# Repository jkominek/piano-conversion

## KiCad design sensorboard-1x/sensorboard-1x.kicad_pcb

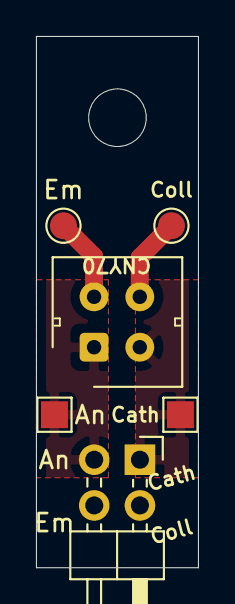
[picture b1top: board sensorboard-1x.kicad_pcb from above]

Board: 2 copper layers, 9.0 x 29.5 mm, 7 parts (0 on the bottom side), 4 nets.

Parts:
An1: TestPoint; TestPoint_Pad_1.5x1.5mm
Cath1: TestPoint; TestPoint_Pad_1.5x1.5mm
Coll1: TestPoint; TestPoint_Pad_D1.5mm
Emit1: TestPoint; TestPoint_Pad_D1.5mm
H1: MountingHole; MountingHole_3.2mm_M3
J1: Conn_02x02_Odd_Even; Pin_Header_Angled_2x02_Pitch2.54mm
U1: CNY70; Vishay_CNY70

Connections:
/Anode: An1.1, J1.3, U1.1
/Cathode: Cath1.1, J1.1, U1.2
/Collector: Coll1.1, J1.2, U1.3
/Emitter: Emit1.1, J1.4, U1.4

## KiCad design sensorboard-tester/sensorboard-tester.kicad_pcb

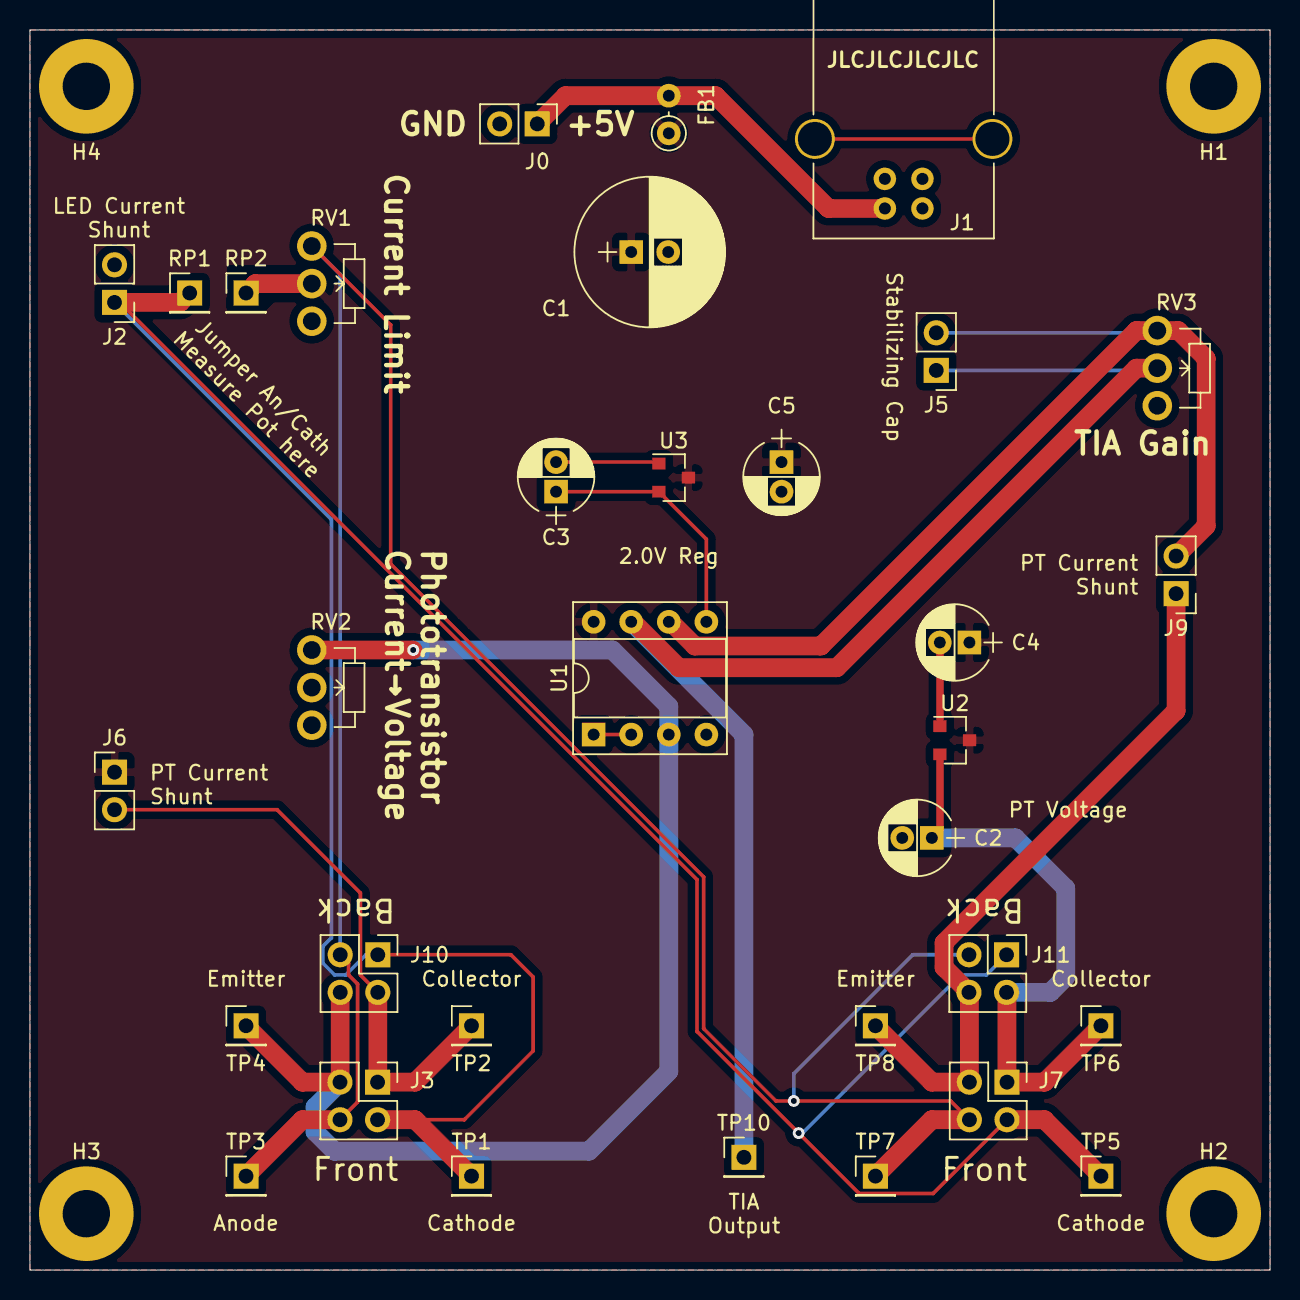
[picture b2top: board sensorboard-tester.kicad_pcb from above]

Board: 2 copper layers, 83.8 x 83.8 mm, 37 parts (0 on the bottom side), 13 nets.

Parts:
C1: C_Small; CP_Radial_D10.0mm_P2.50mm
C2, C4: 10uF; CP_Radial_D5.0mm_P2.00mm
C3, C5: 1uF; CP_Radial_D5.0mm_P2.00mm
FB1: Ferrite_Bead_Small; L_Axial_L5.3mm_D2.2mm_P2.54mm_Vertical_Vishay_IM-1
H1, H2, H3, H4: MountingHole_Pad; MountingHole_3.2mm_M3_Pad
J0: Power; Pin_Header_Straight_1x02_Pitch2.54mm
J1: USB_B
J2: LEDCurrentShunt; Pin_Header_Straight_1x02_Pitch2.54mm
J3, J7, J11: Sensor; Pin_Header_Straight_2x02_Pitch2.54mm
J5: StabilizingCap; Pin_Header_Straight_1x02_Pitch2.54mm
J6, J9: PTCurrentShunt; Pin_Header_Straight_1x02_Pitch2.54mm
J10: MirrorSensor; Pin_Header_Straight_2x02_Pitch2.54mm
RP1, RP2: TestPoint_Probe; Pin_Header_Straight_1x01_Pitch2.54mm
RV1, RV2, RV3: R_POT; Potentiometer_WirePads_Small
TP1, TP2, TP3, TP4, TP5, TP6, TP7, TP8, TP10: TestPoint_Probe; Pin_Header_Straight_1x01_Pitch2.54mm
U1: Opamp_Dual_Generic; DIP-8_W7.62mm_Socket
U2: AP2120N-3.3TRG1; SOT-23
U3: MCP1700T-2002E/TT; SOT-23

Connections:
+3V3: C2.1, J7.1, J11.2, TP6.1, U2.2
+5V: C1.1, C4.1, C5.1, FB1.1, J6.1, RP2.1, RV1.2, U1.8, U2.3, U3.3
/Anode: J3.4, J7.4, J10.3, J11.3, RV1.1, TP3.1, TP7.1
/Cathode: J2.1, J3.2, J7.2, J10.1, J11.1, RP1.1, TP1.1, TP5.1
/Simple/Collector: J3.1, J6.2, J10.2, TP2.1
/Simple/OP+: J3.3, J10.4, RV2.1, TP4.1, U1.3
/Simple/OP-: U1.1, U1.2
/Transimpedance/Emitter: J7.3, J9.1, J11.4, TP8.1
/Transimpedance/OP+: C3.1, U1.5, U3.2
/Transimpedance/OP-: J5.2, J9.2, RV3.1, U1.6
/Transimpedance/OP_OUT: J5.1, RV3.2, TP10.1, U1.7
GND: C1.2, C2.2, C3.2, C4.2, C5.2, H1.1, H2.1, H3.1, H4.1, J0.2, J1.4, J2.2, RV2.2, U1.4, U2.1, U3.1
unnamed: FB1.2, J0.1, J1.1

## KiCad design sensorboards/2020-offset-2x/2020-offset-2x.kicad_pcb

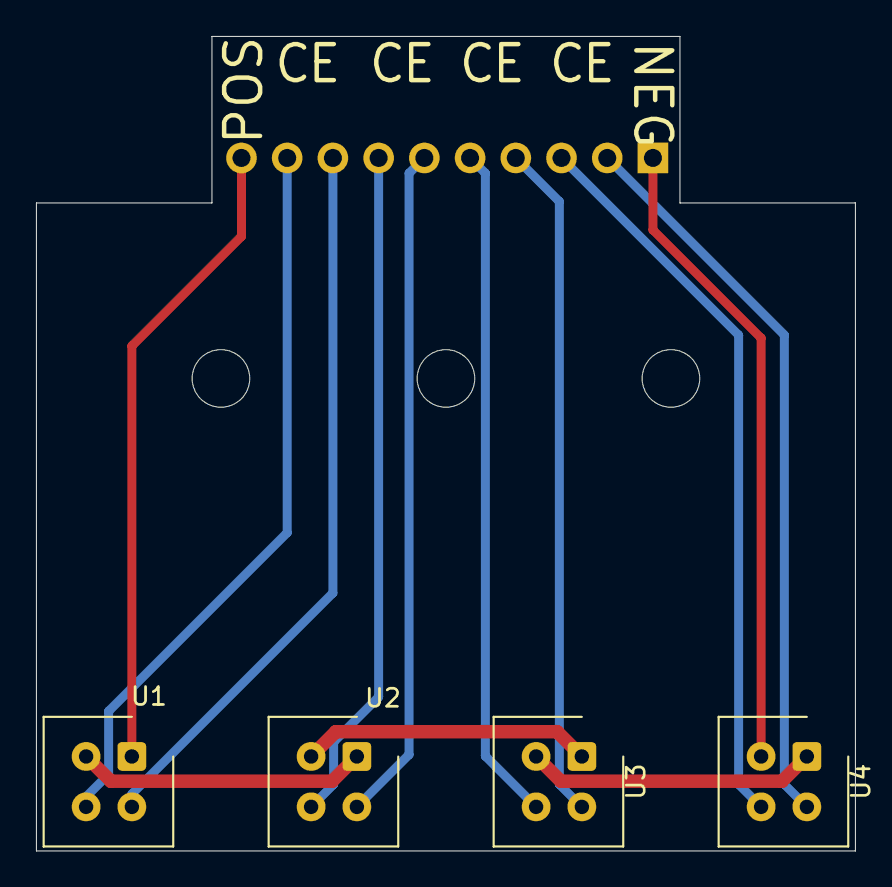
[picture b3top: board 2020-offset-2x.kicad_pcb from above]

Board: 2 copper layers, 45.5 x 45.2 mm, 8 parts (1 on the bottom side), 13 nets.

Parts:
H1, H2, H3: MountingHole; MountingHole_3.2mm_M3
J1: Conn_01x10_Male; Pin_Header_Angled_1x10_Pitch2.54mm
U1, U2, U3, U4: CNY70; Vishay_CNY70

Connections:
/C1: J1.9, U1.3
/C2: J1.7, U2.3
/C3: J1.5, U3.3
/C4: J1.3, U4.3
/E1: J1.8, U1.4
/E2: J1.6, U2.4
/E3: J1.4, U3.4
/E4: J1.2, U4.4
/NEG: J1.1, U4.2
/POS: J1.10, U1.1
unnamed: U1.2, U2.1
unnamed: U2.2, U3.1
unnamed: U3.2, U4.1

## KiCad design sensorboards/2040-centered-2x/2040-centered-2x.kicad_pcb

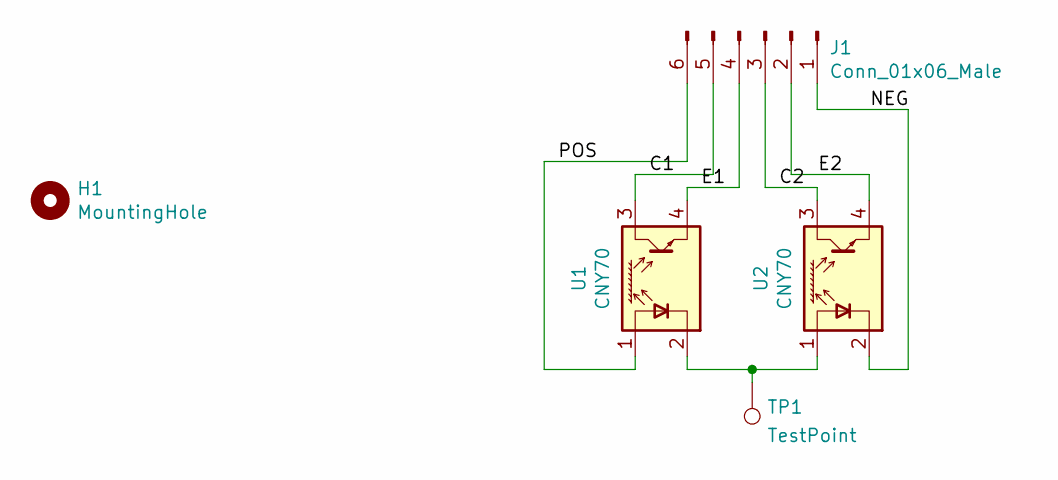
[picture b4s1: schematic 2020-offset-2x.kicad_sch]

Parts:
H1: MountingHole; MountingHole_3.2mm_M3
J1: Conn_01x06_Male; Pin_Header_Angled_1x06_Pitch2.54mm
TP1: TestPoint; TestPoint_Pad_1.0x1.0mm
U1, U2: CNY70; Vishay_CNY70

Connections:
/NEG: J1.1, U2.2 (K)
/POS: J1.6, U1.1 (A)
unnamed: J1.2, U2.4 (E)
unnamed: J1.3, U2.3 (C)
unnamed: J1.4, U1.4 (E)
unnamed: J1.5, U1.3 (C)
unnamed: TP1.1, U1.2 (K), U2.1 (A)

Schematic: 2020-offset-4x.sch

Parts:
H1: MountingHole; MountingHole_3.2mm_M3
J1: Conn_01x06_Male; Pin_Header_Angled_1x06_Pitch2.54mm
U1, U2: CNY70; Vishay_CNY70

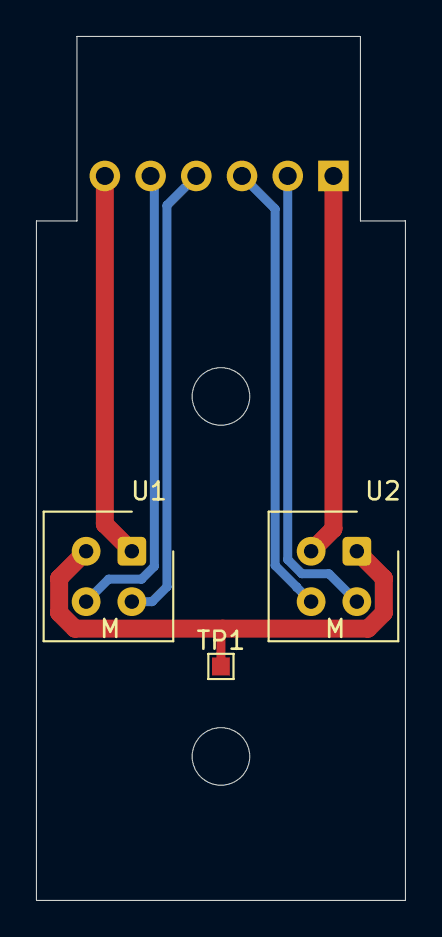
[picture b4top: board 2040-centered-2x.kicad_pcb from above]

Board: 2 copper layers, 20.5 x 48.0 mm, 6 parts (1 on the bottom side), 7 nets.

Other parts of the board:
H2: MountingHole; MountingHole_3.2mm_M3

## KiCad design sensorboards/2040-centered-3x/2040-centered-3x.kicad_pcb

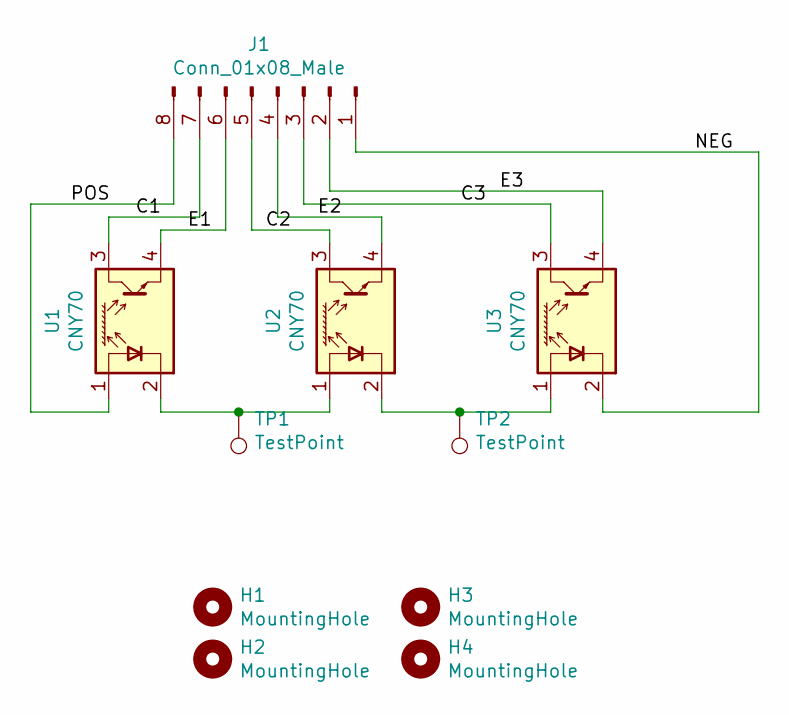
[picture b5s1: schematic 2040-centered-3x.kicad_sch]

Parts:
H1, H2, H3, H4: MountingHole; MountingHole_3.2mm_M3
J1: Conn_01x08_Male; PinHeader_1x08_P2.54mm_Horizontal
TP1, TP2: TestPoint; TestPoint_Pad_1.0x1.0mm
U1, U2, U3: CNY70; Vishay_CNY70

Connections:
/C1: J1.7, U1.3 (C)
/C2: J1.5, U2.3 (C)
/C3: J1.3, U3.3 (C)
/E1: J1.6, U1.4 (E)
/E2: J1.4, U2.4 (E)
/E3: J1.2, U3.4 (E)
/NEG: J1.1, U3.2 (K)
/POS: J1.8, U1.1 (A)
unnamed: TP1.1, U1.2 (K), U2.1 (A)
unnamed: TP2.1, U2.2 (K), U3.1 (A)

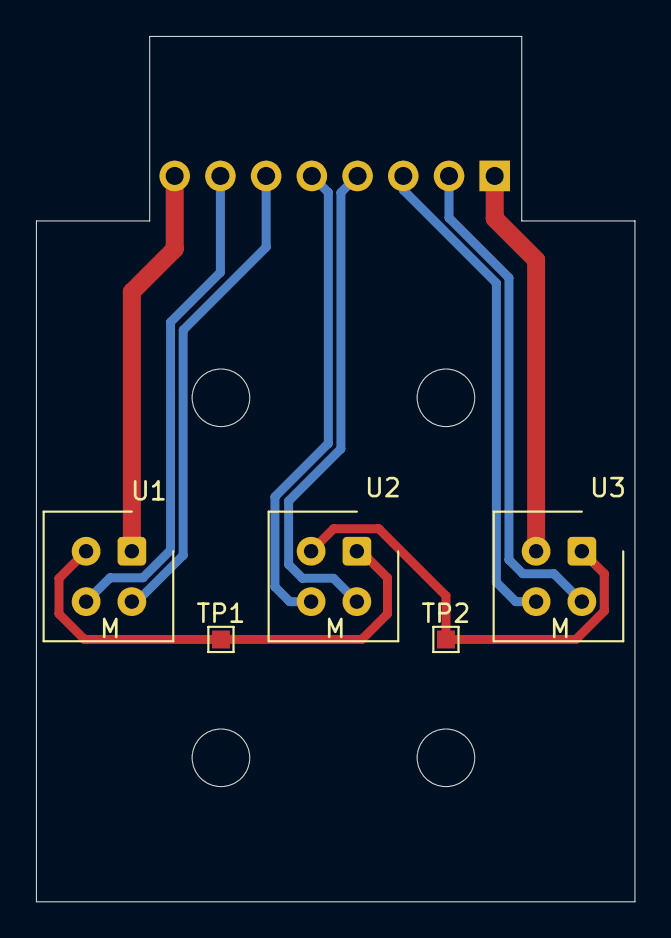
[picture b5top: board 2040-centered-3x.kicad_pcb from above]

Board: 2 copper layers, 33.2 x 48.1 mm, 10 parts (1 on the bottom side), 10 nets.
